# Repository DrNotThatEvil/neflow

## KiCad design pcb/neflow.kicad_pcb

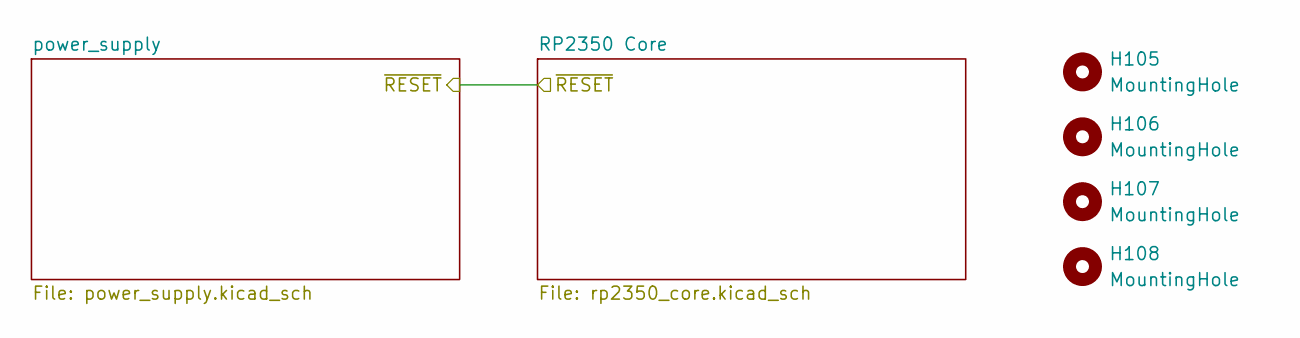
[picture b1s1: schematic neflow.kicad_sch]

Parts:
H105, H106, H107, H108: MountingHole; MountingHole_3mm

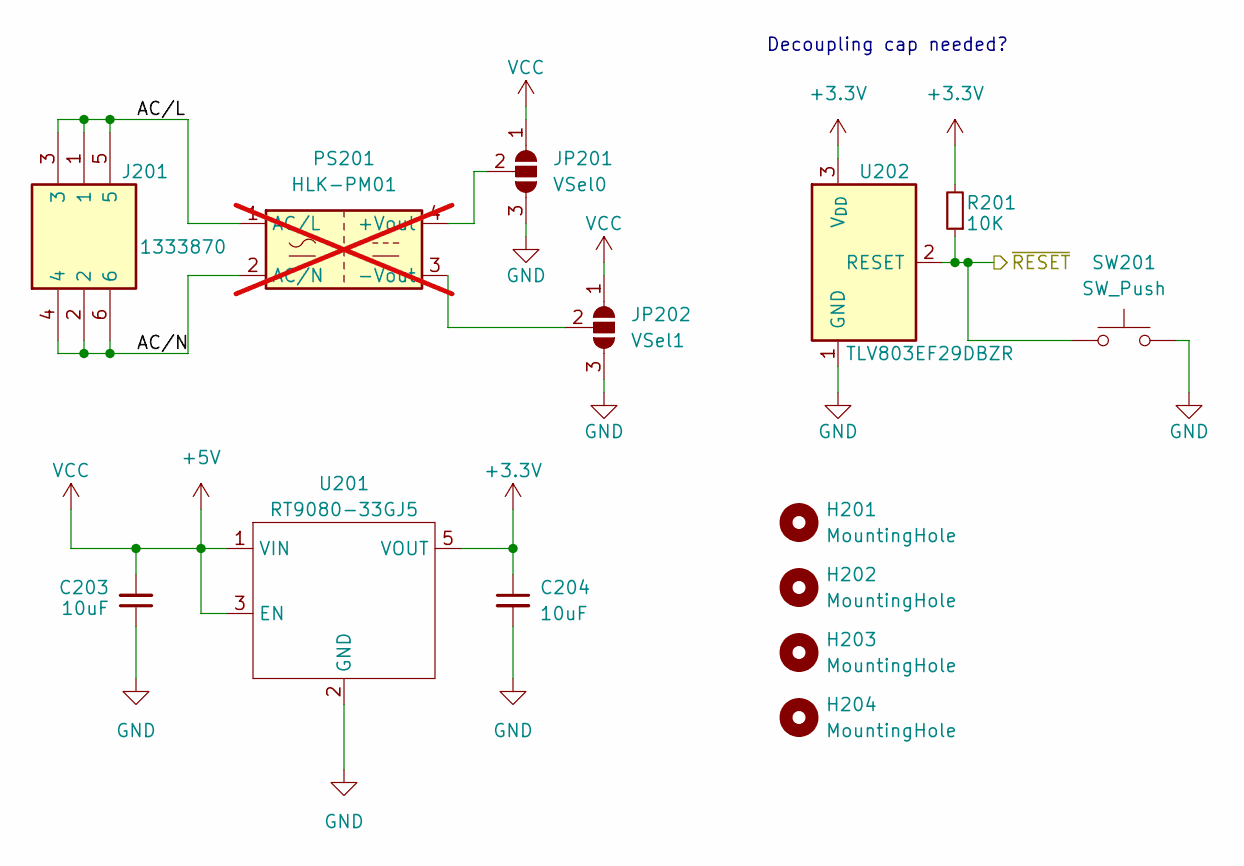
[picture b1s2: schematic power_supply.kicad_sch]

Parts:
C203, C204: 10uF; R_0603_1608Metric; LCSC C19702
H201, H202, H203, H204: MountingHole; MountingHole_3mm
J201: 1333870; Manufacturer_Part_Number 1333870; Mouser Part Number 651-1333870
JP201: VSel0; SolderJumper-3_P1.3mm_Open_Pad1.0x1.5mm
JP202: VSel1; SolderJumper-3_P1.3mm_Open_Pad1.0x1.5mm
PS201: HLK-PM01; Converter_ACDC_HiLink_HLK-PMxx; not fitted
R201: 10K; R_0603_1608Metric; LCSC C25804
SW201: SW_Push; BUTTON_SILICON
U201: RT9080-33GJ5; TSOT-23-5
U202: TLV803EF29DBZR; SOT-23; LCSC C2868252

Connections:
+3.3V: C204.1, R201.2, U201.5 (VOUT), U202.3 (V_{DD}); also elsewhere on the board
+5V: C203.2, JP201.1 (A), JP202.1 (A), U201.1 (VIN), U201.3 (EN); also elsewhere on the board
/power_supply/AC/L: J201.1, J201.3, J201.5, PS201.1 (AC/L)
/power_supply/AC/N: J201.2, J201.4, J201.6, PS201.2 (AC/N)
/power_supply/~RESET: R201.1, SW201.2, U202.2 (RESET)
GND: C203.1, C204.2, JP201.3 (B), JP202.3 (B), SW201.1, U201.2 (GND), U202.1 (GND); also elsewhere on the board
unnamed: JP201.2 (C), PS201.4 (+Vout)
unnamed: JP202.2 (C), PS201.3 (-Vout)

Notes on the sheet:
Decoupling cap needed?

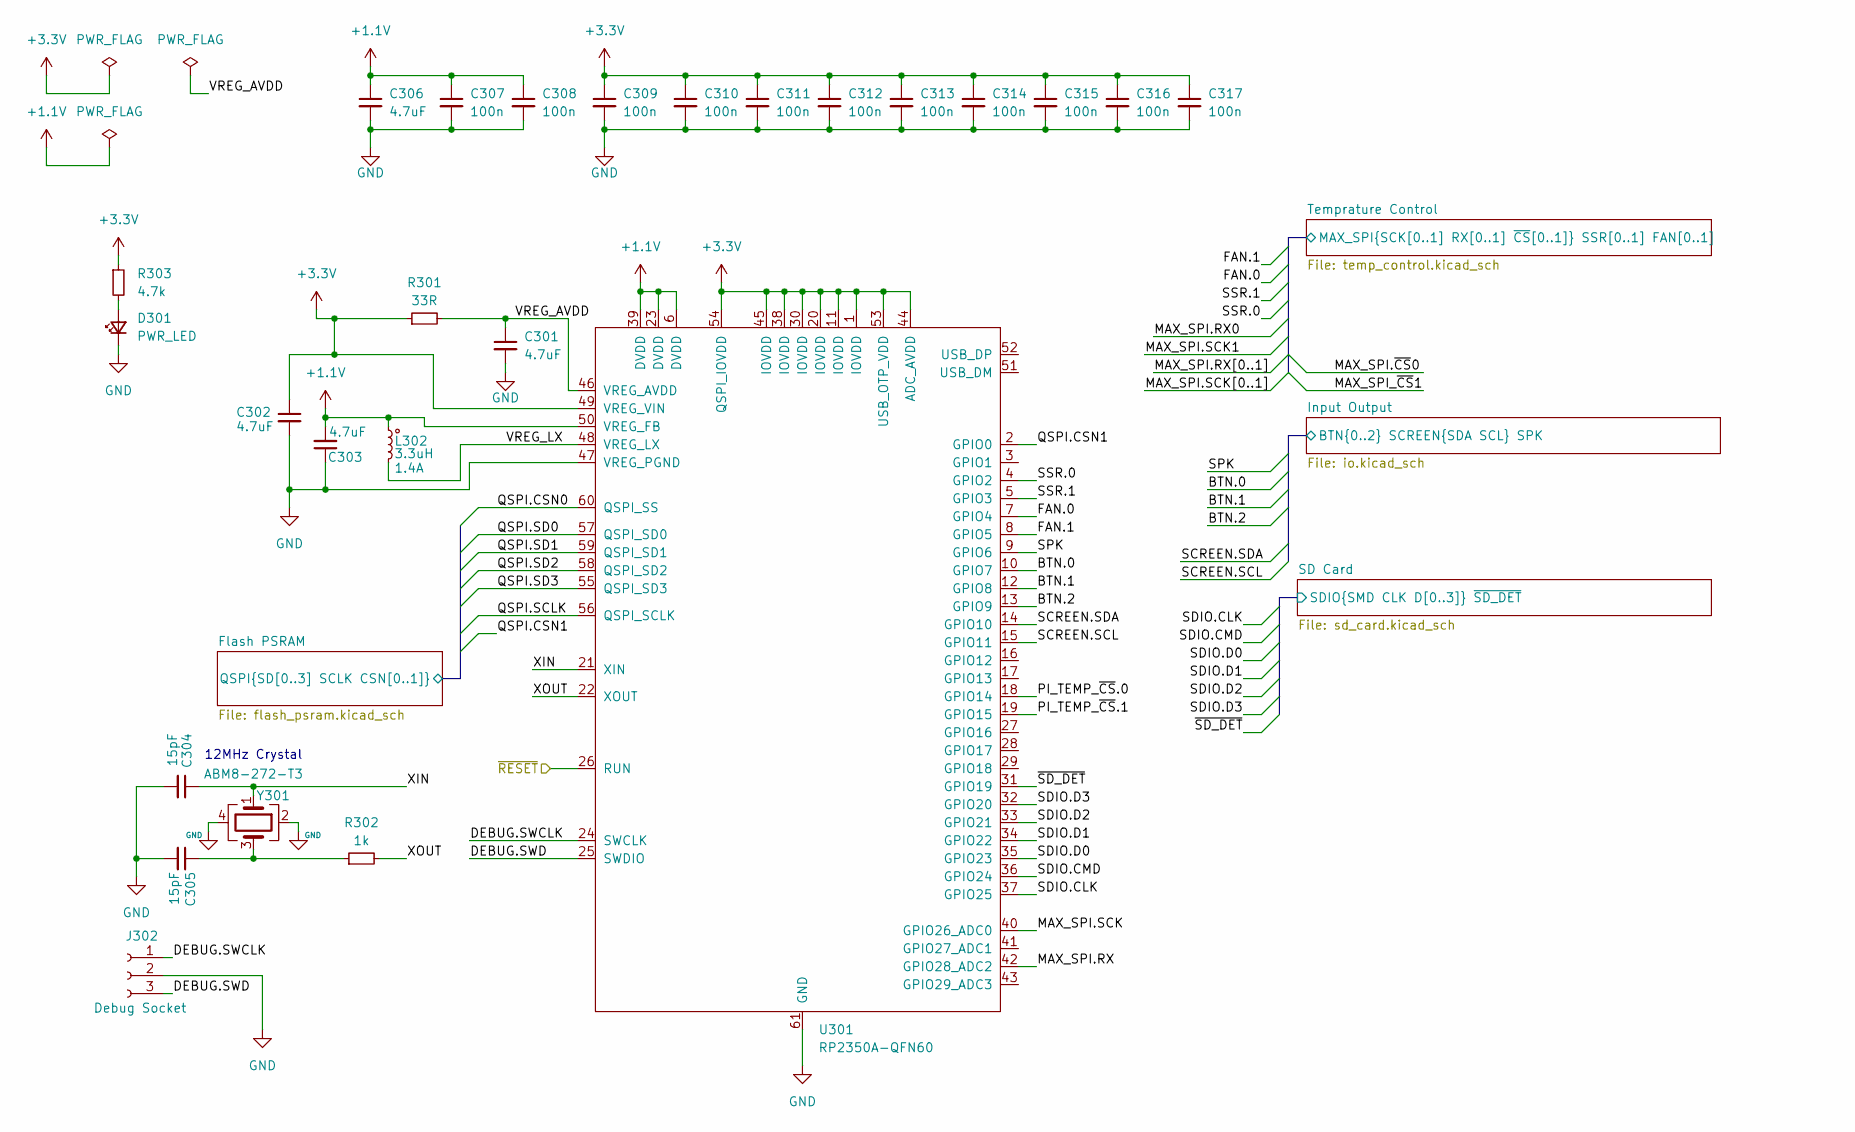
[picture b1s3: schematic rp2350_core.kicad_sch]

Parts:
C301, C302, C303, C306: 4.7uF; R_0603_1608Metric
C304, C305: 15pF; R_0603_1608Metric
C307, C308, C309, C310, C311, C312, C313, C314, C315, C316, C317: 100n; R_0603_1608Metric
D301: PWR_LED; LED_0805_2012Metric
J302: Debug Socket; JST_XH_B3B-XH-AM_1x03_P2.50mm_Vertical
L302: 3.3uH; 0806_Polarized
R301: 33R; R_0603_1608Metric
R302: 1k; R_0603_1608Metric
R303: 4.7k; R_0603_1608Metric
U301: RP2350A-QFN60; QFN-60-1EP_7x7mm_P0.4mm_EP3.4x3.4mm_ThermalVias
Y301: ABM8-272-T3; Crystal_SMD_3.2x2.5mm

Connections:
+1.1V: C303.2, C306.1, C307.1, C308.1, L302.1, U301.6 (DVDD), U301.23 (DVDD), U301.39 (DVDD), U301.50 (VREG_FB)
+3.3V: C302.1, C309.1, C310.1, C311.1, C312.1, C313.1, C314.1, C315.1, C316.1, C317.1, R301.1, R303.1, U301.1 (IOVDD), U301.11 (IOVDD), U301.20 (IOVDD), U301.30 (IOVDD), U301.38 (IOVDD), U301.44 (ADC_AVDD), U301.45 (IOVDD), U301.49 (VREG_VIN), U301.53 (USB_OTP_VDD), U301.54 (QSPI_IOVDD); also elsewhere on the board
/RP2350 Core/BTN.0: U301.10 (GPIO7)
/RP2350 Core/BTN.1: U301.12 (GPIO8)
/RP2350 Core/BTN.2: U301.13 (GPIO9)
/RP2350 Core/DEBUG.SWCLK: J302.1, U301.24 (SWCLK)
/RP2350 Core/DEBUG.SWD: J302.3, U301.25 (SWDIO)
/RP2350 Core/FAN.0: U301.7 (GPIO4)
/RP2350 Core/FAN.1: U301.8 (GPIO5)
/RP2350 Core/Flash PSRAM/QSPI.CSN0: U301.60 (QSPI_SS); also elsewhere on the board
/RP2350 Core/Flash PSRAM/QSPI.CSN1: U301.2 (GPIO0); also elsewhere on the board
/RP2350 Core/Flash PSRAM/QSPI.SCLK: U301.56 (QSPI_SCLK); also elsewhere on the board
/RP2350 Core/Flash PSRAM/QSPI.SD0: U301.57 (QSPI_SD0); also elsewhere on the board
/RP2350 Core/Flash PSRAM/QSPI.SD1: U301.59 (QSPI_SD1); also elsewhere on the board
/RP2350 Core/Flash PSRAM/QSPI.SD2: U301.58 (QSPI_SD2); also elsewhere on the board
/RP2350 Core/Flash PSRAM/QSPI.SD3: U301.55 (QSPI_SD3); also elsewhere on the board
/RP2350 Core/PI_TEMP_~CS.0: U301.18 (GPIO14)
/RP2350 Core/PI_TEMP_~CS.1: U301.19 (GPIO15)
/RP2350 Core/SCREEN.SCL: U301.15 (GPIO11)
/RP2350 Core/SCREEN.SDA: U301.14 (GPIO10)
/RP2350 Core/SD Card/SDIO.CLK: U301.37 (GPIO25); also elsewhere on the board
/RP2350 Core/SD Card/SDIO.D0: U301.35 (GPIO23); also elsewhere on the board
/RP2350 Core/SD Card/SDIO.D1: U301.34 (GPIO22); also elsewhere on the board
/RP2350 Core/SD Card/SDIO.D2: U301.33 (GPIO21); also elsewhere on the board
/RP2350 Core/SD Card/SDIO.D3: U301.32 (GPIO20); also elsewhere on the board
/RP2350 Core/SDIO.CMD: U301.36 (GPIO24)
/RP2350 Core/SPK: U301.9 (GPIO6)
/RP2350 Core/SSR.0: U301.4 (GPIO2)
/RP2350 Core/SSR.1: U301.5 (GPIO3)
/RP2350 Core/Temprature Control/MAX_SPI.RX: U301.16 (GPIO12); also elsewhere on the board
/RP2350 Core/Temprature Control/MAX_SPI.SCK: U301.17 (GPIO13); also elsewhere on the board
/RP2350 Core/VREG_AVDD: C301.1, R301.2, U301.46 (VREG_AVDD)
/RP2350 Core/VREG_LX: L302.2, U301.48 (VREG_LX)
/RP2350 Core/XIN: C304.1, U301.21 (XIN), Y301.1
/RP2350 Core/XOUT: R302.2, U301.22 (XOUT)
/RP2350 Core/~RESET: U301.26 (RUN)
/RP2350 Core/~SD_DET: U301.31 (GPIO19)
GND: C301.2, C302.2, C303.1, C304.2, C305.2, C306.2, C307.2, C308.2, C309.2, C310.2, C311.2, C312.2, C313.2, C314.2, C315.2, C316.2, C317.2, D301.1 (K), J302.2, U301.47 (VREG_PGND), U301.61 (GND), Y301.2, Y301.4; also elsewhere on the board
unnamed: C305.1, R302.1, Y301.3
unnamed: D301.2 (A), R303.2

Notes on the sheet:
12MHz Crystal

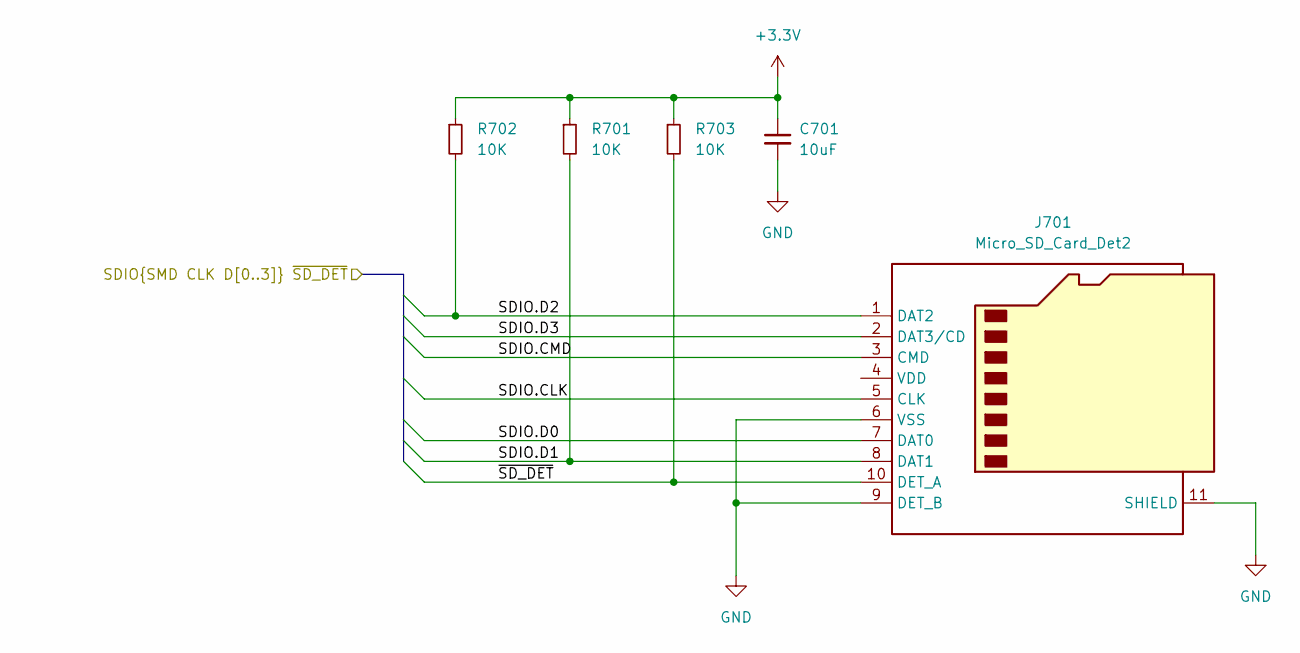
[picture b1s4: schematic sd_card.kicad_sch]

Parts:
C701: 10uF; R_0603_1608Metric
J701: Micro_SD_Card_Det2; microSD_HC_Hirose_DM3AT-SF-PEJM5
R701, R702, R703: 10K; R_0603_1608Metric

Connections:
+3.3V: C701.1, R701.1, R702.1, R703.1; also elsewhere on the board
/RP2350 Core/SD Card/SDIO.CLK: J701.5 (CLK); also elsewhere on the board
/RP2350 Core/SD Card/SDIO.CMD: J701.3 (CMD)
/RP2350 Core/SD Card/SDIO.D0: J701.7 (DAT0); also elsewhere on the board
/RP2350 Core/SD Card/SDIO.D1: J701.8 (DAT1), R701.2; also elsewhere on the board
/RP2350 Core/SD Card/SDIO.D2: J701.1 (DAT2), R702.2; also elsewhere on the board
/RP2350 Core/SD Card/SDIO.D3: J701.2 (DAT3/CD); also elsewhere on the board
/RP2350 Core/SD Card/~SD_DET: J701.10 (DET_A), R703.2
GND: C701.2, J701.6 (VSS), J701.9 (DET_B), J701.11 (SHIELD); also elsewhere on the board

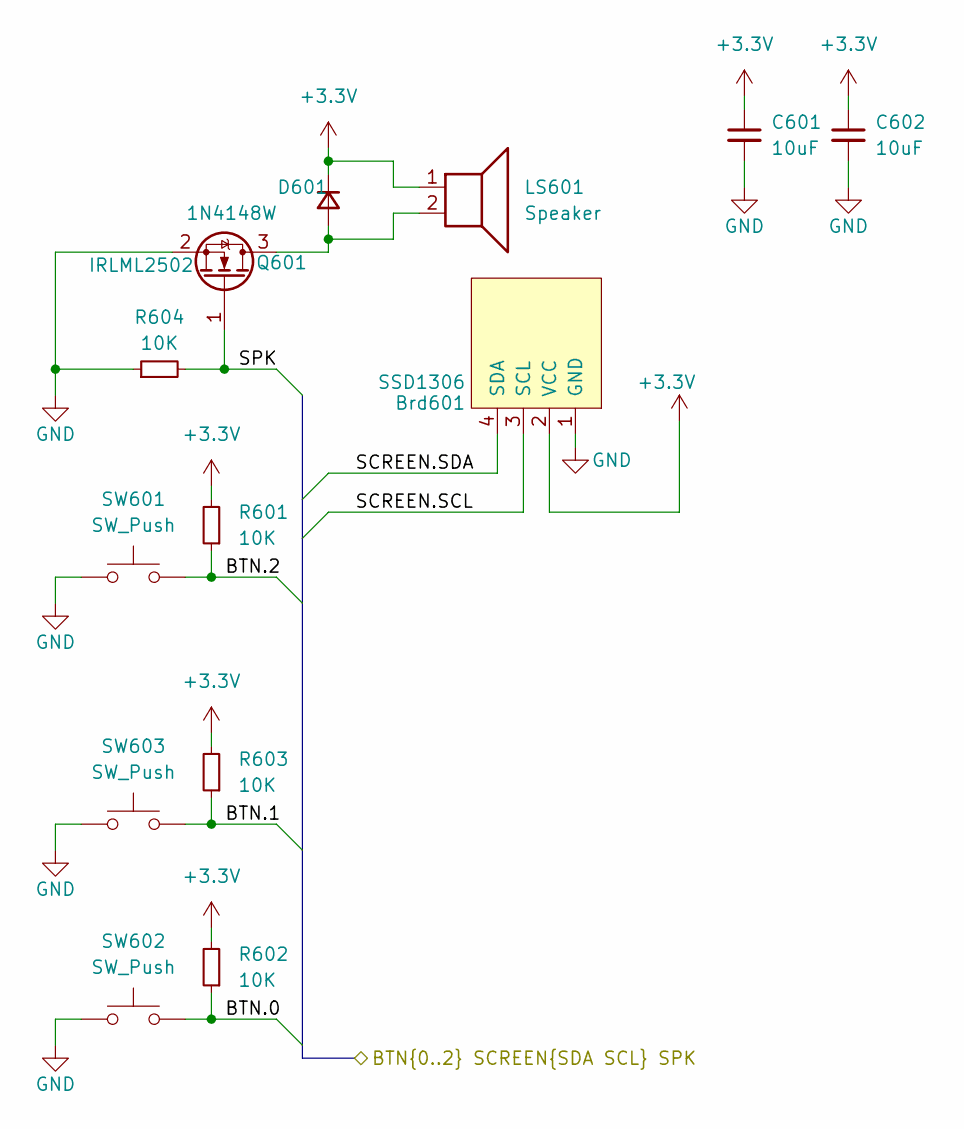
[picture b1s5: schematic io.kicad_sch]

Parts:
Brd601: SSD1306; 128x64OLED
C601, C602: 10uF; R_0603_1608Metric; LCSC C19702
D601: 1N4148W; D_SOD-123; LCSC C81598
LS601: Speaker; PassiveBuzzerSMD_JiangsuHuaneng_MLT-5030
Q601: IRLML2502; SOT-23; LCSC C2589
R601, R602, R603, R604: 10K; R_0603_1608Metric; LCSC C25804
SW601, SW602, SW603: SW_Push; BUTTON_SILICON

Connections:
+3.3V: Brd601.2 (VCC), C601.1, C602.1, D601.1 (K), LS601.1, R601.2, R602.2, R603.2; also elsewhere on the board
/RP2350 Core/Input Output/BTN.0: R602.1, SW602.2
/RP2350 Core/Input Output/BTN.1: R603.1, SW603.2
/RP2350 Core/Input Output/BTN.2: R601.1, SW601.2
/RP2350 Core/Input Output/SCREEN.SCL: Brd601.3 (SCL)
/RP2350 Core/Input Output/SCREEN.SDA: Brd601.4 (SDA)
/RP2350 Core/Input Output/SPK: Q601.1 (G), R604.2
GND: Brd601.1 (GND), C601.2, C602.2, Q601.2 (S), R604.1, SW601.1, SW602.1, SW603.1; also elsewhere on the board
unnamed: D601.2 (A), LS601.2, Q601.3 (D)

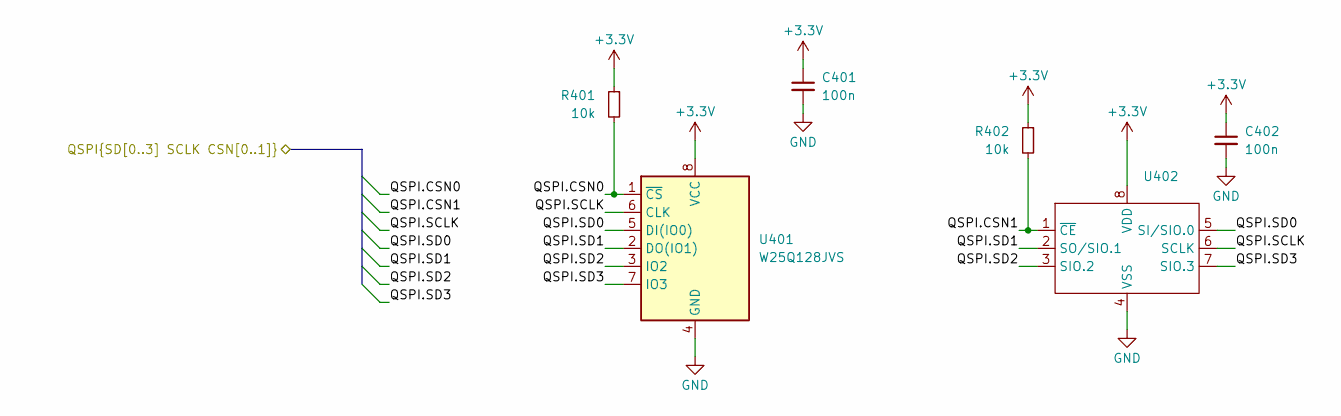
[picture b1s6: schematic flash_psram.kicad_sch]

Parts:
C401, C402: 100n; R_0603_1608Metric
R401, R402: 10k; R_0603_1608Metric
U401: W25Q128JVS; SOIC-8_5.23x5.23mm_P1.27mm
U402: SOIC-8_3.9x4.9mm_P1.27mm

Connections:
+3.3V: C401.1, C402.1, R401.1, R402.1, U401.8 (VCC), U402.8 (VDD); also elsewhere on the board
/RP2350 Core/Flash PSRAM/QSPI.CSN0: R401.2, U401.1 (~CS); also elsewhere on the board
/RP2350 Core/Flash PSRAM/QSPI.CSN1: R402.2, U402.1 (~CE); also elsewhere on the board
/RP2350 Core/Flash PSRAM/QSPI.SCLK: U401.6 (CLK), U402.6 (SCLK); also elsewhere on the board
/RP2350 Core/Flash PSRAM/QSPI.SD0: U401.5 (DI(IO0)), U402.5 (SI/SIO.0); also elsewhere on the board
/RP2350 Core/Flash PSRAM/QSPI.SD1: U401.2 (DO(IO1)), U402.2 (SO/SIO.1); also elsewhere on the board
/RP2350 Core/Flash PSRAM/QSPI.SD2: U401.3 (IO2), U402.3 (SIO.2); also elsewhere on the board
/RP2350 Core/Flash PSRAM/QSPI.SD3: U401.7 (IO3), U402.7 (SIO.3); also elsewhere on the board
GND: C401.2, C402.2, U401.4 (GND), U402.4 (VSS); also elsewhere on the board

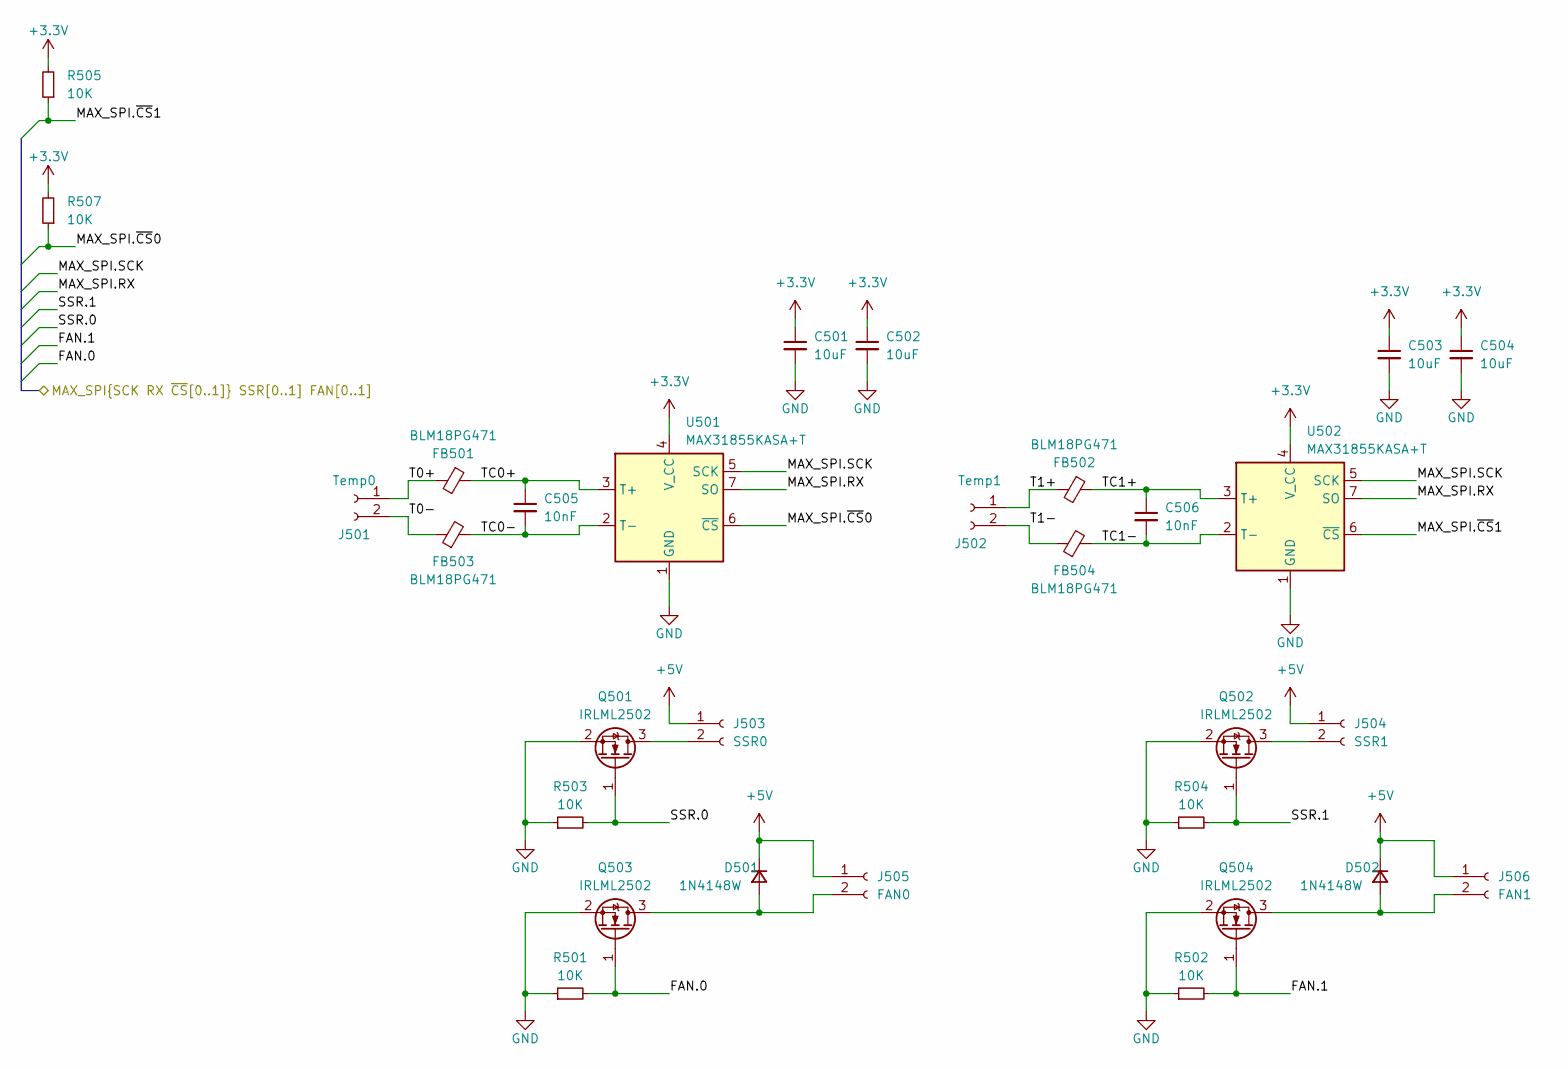
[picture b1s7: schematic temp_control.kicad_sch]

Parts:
C501, C502, C503, C504: 10uF; R_0603_1608Metric; LCSC C19702
C505, C506: 10nF; R_0603_1608Metric; LCSC C57112
D501, D502: 1N4148W; D_SOD-123; LCSC C81598
FB501, FB502, FB503, FB504: BLM18PG471; R_0603_1608Metric; LCSC C97853
J501: Temp0; JST_XH_B2B-XH-AM_1x02_P2.50mm_Vertical
J502: Temp1; JST_XH_B2B-XH-AM_1x02_P2.50mm_Vertical
J503: SSR0; JST_XH_B2B-XH-AM_1x02_P2.50mm_Vertical
J504: SSR1; JST_XH_B2B-XH-AM_1x02_P2.50mm_Vertical
J505: FAN0; JST_XH_B2B-XH-AM_1x02_P2.50mm_Vertical
J506: FAN1; JST_XH_B2B-XH-AM_1x02_P2.50mm_Vertical
Q501, Q502, Q503, Q504: IRLML2502; SOT-23; LCSC C2589
R501, R502, R503, R504, R505, R507: 10K; R_0603_1608Metric; LCSC C25804
U501, U502: MAX31855KASA+T; SOIC-8_3.9x4.9mm_P1.27mm; LCSC C52028

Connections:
+3.3V: C501.1, C502.1, C503.1, C504.1, R505.2, R507.2, U501.4 (V_CC), U502.4 (V_CC); also elsewhere on the board
+5V: D501.1 (K), D502.1 (K), J503.1, J504.1, J505.1, J506.1; also elsewhere on the board
/RP2350 Core/Temprature Control/FAN.0: Q503.1 (G), R501.2
/RP2350 Core/Temprature Control/FAN.1: Q504.1 (G), R502.2
/RP2350 Core/Temprature Control/MAX_SPI.RX: U501.7 (SO), U502.7 (SO); also elsewhere on the board
/RP2350 Core/Temprature Control/MAX_SPI.SCK: U501.5 (SCK), U502.5 (SCK); also elsewhere on the board
/RP2350 Core/Temprature Control/PI_TEMP_~CS.0: R507.1, U501.6 (~CS)
/RP2350 Core/Temprature Control/PI_TEMP_~CS.1: R505.1, U502.6 (~CS)
/RP2350 Core/Temprature Control/SSR.0: Q501.1 (G), R503.2
/RP2350 Core/Temprature Control/SSR.1: Q502.1 (G), R504.2
/RP2350 Core/Temprature Control/T0+: FB501.2, J501.1
/RP2350 Core/Temprature Control/T0-: FB503.1, J501.2
/RP2350 Core/Temprature Control/T1+: FB502.2, J502.1
/RP2350 Core/Temprature Control/T1-: FB504.1, J502.2
/RP2350 Core/Temprature Control/TC0+: C505.1, FB501.1, U501.3 (T+)
/RP2350 Core/Temprature Control/TC0-: C505.2, FB503.2, U501.2 (T-)
/RP2350 Core/Temprature Control/TC1+: C506.1, FB502.1, U502.3 (T+)
/RP2350 Core/Temprature Control/TC1-: C506.2, FB504.2, U502.2 (T-)
GND: C501.2, C502.2, C503.2, C504.2, Q501.2 (S), Q502.2 (S), Q503.2 (S), Q504.2 (S), R501.1, R502.1, R503.1, R504.1, U501.1 (GND), U502.1 (GND); also elsewhere on the board
unnamed: D501.2 (A), J505.2, Q503.3 (D)
unnamed: D502.2 (A), J506.2, Q504.3 (D)
unnamed: J503.2, Q501.3 (D)
unnamed: J504.2, Q502.3 (D)

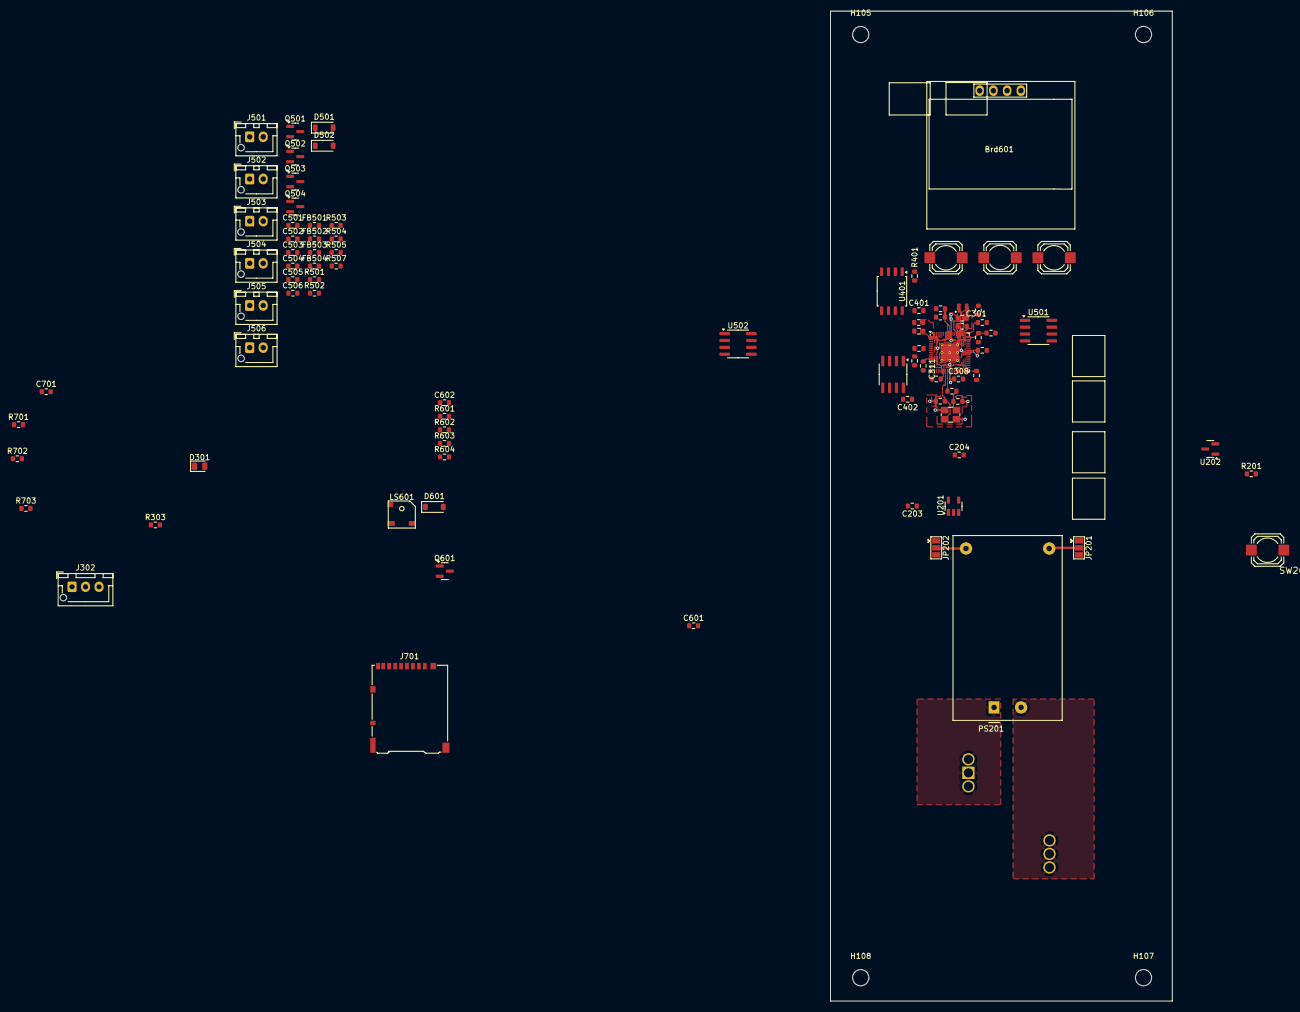
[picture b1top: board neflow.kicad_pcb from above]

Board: 4 copper layers, 63.2 x 183.1 mm, 97 parts (1 on the bottom side), 55 nets.

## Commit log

2023-10-15 Working on menu
2023-10-15 WIP: Working on menu
2023-10-16 WIP working on nf_menu
2023-10-16 WIP: Menu system with up/down
2023-10-22 WIP: Adding empty pcb project
2023-10-22 WIP: Schematic rev0 almost done
2023-10-23 WIP: Adding button footprint
2023-10-26 Menu system rotation
2023-10-29 WIP: Switching to laptop
2023-10-30 WIP: Edit and view profile flow added
2023-10-30 Remove animation delay
2023-10-30 Starting to split screens in appropriate sections and files
2023-10-31 Pushing notes
2023-11-01 Basic new flow for cleanup structure
2023-11-02 Add silicone_btn and pcb
2023-11-02 WIP: Finished new profiles menu
2023-11-04 WIP: Adding new edit screen base
2023-11-05 WIP: additing value edit arrows
2023-11-05 WIP: Editing value
2023-11-05 WIP: added back button to the new edit screen
2023-11-06 Adding almost finished schematic
2023-11-07 Added power to pico
2023-11-07 WIP: Switching to workstation
2023-11-07 WIP: Working on pcb
2023-11-08 WIP: changes to pcb
2023-11-09 WIP: Finishing the pcb rev0
2023-11-21 WIP: Switching workstation
2023-11-24 Code changes
2023-11-24 WIP: Switching to desktop
2023-11-25 WIP: Sleepy time
2023-12-01 WIP: Edit menu now uses profile values, time decrease logic added
2023-12-02 WIP: Added config edit screen base
2023-12-03 Added config screen and saving to flash of the config screen
2023-12-03 Extended memory system and added clearing function to test menu
2023-12-04 Finishing memory system bugs:
2023-12-05 Profile screen memory fixes
2023-12-07 Adding profile saving
2023-12-13 WIP: Working on tempsystem
2023-12-16 Working on temp system
2023-12-18 Implemented quick pid and cleaned up the tempsys
2024-01-08 WIP: Begining code cleanup
2024-01-09 WIP: Cleaning up some warnings and some more menu code
2024-01-10 WIP: Cleaned up the nf_menu and nf_config
2024-01-10 WIP: Added todo comment for next time
2024-01-15 Adding graph and tuning tempsys
2024-01-16 WIP: Crude graph drawing added
2024-01-25 WIP: Working on calibration
2024-02-02 Reworking the graph system
2024-02-02 Fixed saving bug added dash line
2024-02-05 WIP stashing changes
2024-02-23 WIP: Switching workstations
2024-02-23 WIP: Switching back
2024-02-24 WIP: Stashing
2024-02-24 WIP: Stashing code switching workstation
2024-03-01 WIP: Stashing code
2024-03-03 WIP: Finishing up for the weekend
2024-06-09 Finishing up the profile run code
2024-06-10 Editing todo.md
2024-06-10 First reflow its a start
2024-06-11 Adding back button and fixing temprature bugs
2024-11-19 Added TLV803E supply voltage supervisor
2024-11-19 Adding new pcb changes for v2 pcb with reset logic
2024-12-05 Removing old TODO's adding clang-format
2024-12-05 Add format on save to settings
2024-12-06 Almost done with todos ready for new pcb interation
2024-12-10 Finished the last big todo's for merge
2024-12-10 Feature/code refactor (#1)
    * Starting to split screens in appropriate sections and files
    * Pushing notes
    * WIP: switching to laptop
    * Basic new flow for cleanup structure
    * Add silicone_btn and pcb
    * WIP: Finished new profiles menu
2024-12-16 Reworking to rp2350 intergrated
2024-12-22 WIP: Stashing work to mess with vm
